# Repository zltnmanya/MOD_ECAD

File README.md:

# MOD schematic

MOD (Modular Orientation Device) [schematic](https://raw.githubusercontent.com/zltnmanya/MOD_ECAD/refs/heads/main/schematic.pdf)

MOD schematic © 2026 by Zoltán Mánya is licensed under CC BY-SA 4.0

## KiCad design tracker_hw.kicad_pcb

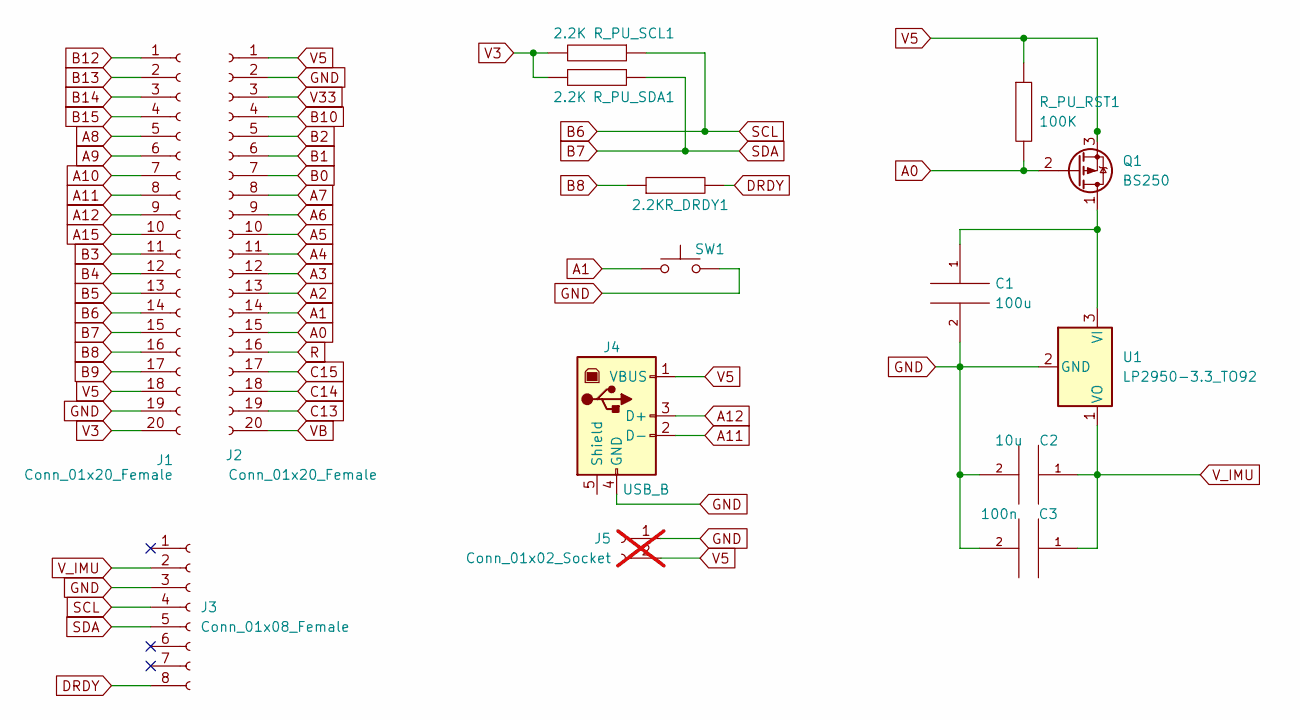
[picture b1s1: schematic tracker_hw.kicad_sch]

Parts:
C1: 100u; CP_Radial_D5.0mm_P2.50mm
C2: 10u; CP_Radial_D5.0mm_P2.50mm
C3: 100n; CP_Radial_D5.0mm_P2.50mm
J1, J2: Conn_01x20_Female; PinSocket_1x20_P2.54mm_Vertical
J3: Conn_01x08_Female; PinSocket_1x08_P2.54mm_Vertical
J4: USB_B; USB_B_Lumberg_2411_02_Horizontal
J5: Conn_01x02_Socket; SolderWire-0.25sqmm_1x02_P4.2mm_D0.65mm_OD1.7mm; not fitted
Q1: BS250; TO-92_Inline
R_DRDY1: 2.2K; R_Axial_DIN0204_L3.6mm_D1.6mm_P2.54mm_Vertical
R_PU_RST1: 100K; R_Axial_DIN0204_L3.6mm_D1.6mm_P2.54mm_Vertical
R_PU_SCL1: 2.2K; R_Axial_DIN0204_L3.6mm_D1.6mm_P2.54mm_Vertical
R_PU_SDA1: 2.2K; R_Axial_DIN0204_L3.6mm_D1.6mm_P2.54mm_Vertical
SW1: SW_Push; SolderWire-0.25sqmm_1x02_P4.2mm_D0.65mm_OD1.7mm
U1: LP2950-3.3_TO92; TO-92_Inline

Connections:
A0: J2.15, Q1.2 (G), R_PU_RST1.2
A1: J2.14, SW1.1
A2: J2.13
A3: J2.12
A4: J2.11
A5: J2.10
A6: J2.9
A7: J2.8
A8: J1.5
A9: J1.6
A10: J1.7
A11: J1.8, J4.2 (D-)
A12: J1.9, J4.3 (D+)
A15: J1.10
B0: J2.7
B1: J2.6
B2: J2.5
B3: J1.11
B4: J1.12
B5: J1.13
B6: J1.14, J3.4, R_PU_SCL1.1
B7: J1.15, J3.5, R_PU_SDA1.1
B8: J1.16, R_DRDY1.1
B9: J1.17
B10: J2.4
B12: J1.1
B13: J1.2
B14: J1.3
B15: J1.4
C13: J2.19
C14: J2.18
C15: J2.17
DRDY: J3.8, R_DRDY1.2
GND: C1.2, C2.2, C3.2, J1.19, J2.2, J3.3, J4.4 (GND), J5.1, SW1.2, U1.2 (GND)
unnamed: C1.1, Q1.1 (D), U1.3 (VI)
R: J2.16
V3: J1.20, R_PU_SCL1.2, R_PU_SDA1.2
V5: J1.18, J2.1, J4.1 (VBUS), J5.2, Q1.3 (S), R_PU_RST1.1
V33: J2.3
VB: J2.20
V_IMU: C2.1, C3.1, J3.2, U1.1 (VO)

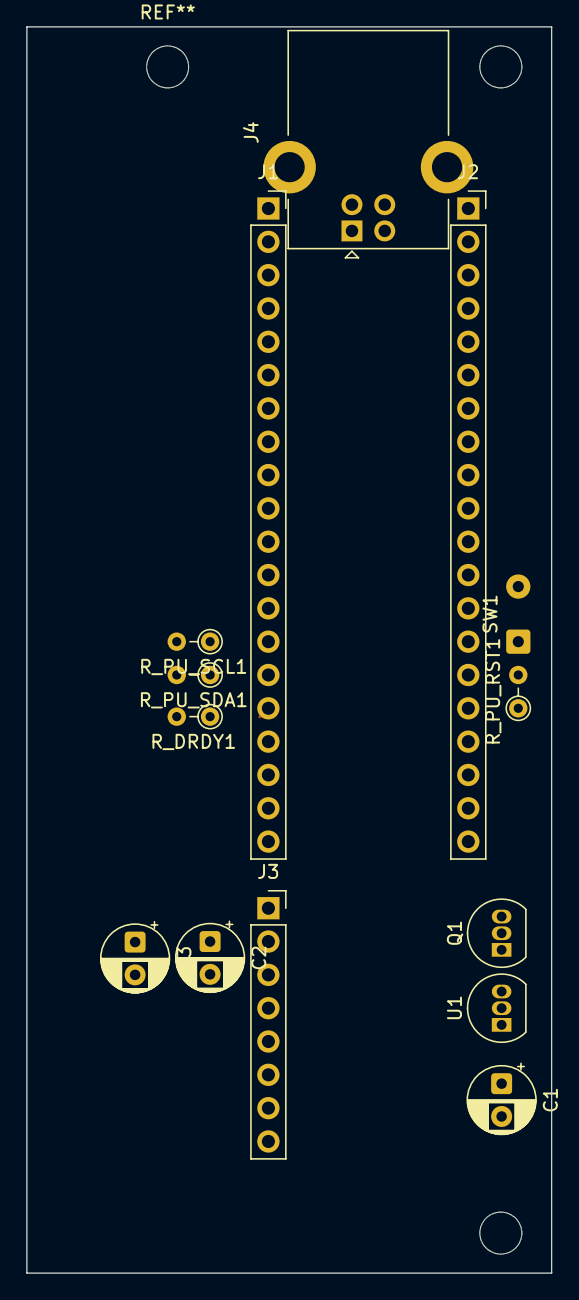
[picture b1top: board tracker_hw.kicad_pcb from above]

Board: 2 copper layers, 40.0 x 95.0 mm, 14 parts (0 on the bottom side), 13 nets.

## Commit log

2026-03-28 export to schematic to schematic.pdf
2026-03-28 Add link to schematic.pdf
